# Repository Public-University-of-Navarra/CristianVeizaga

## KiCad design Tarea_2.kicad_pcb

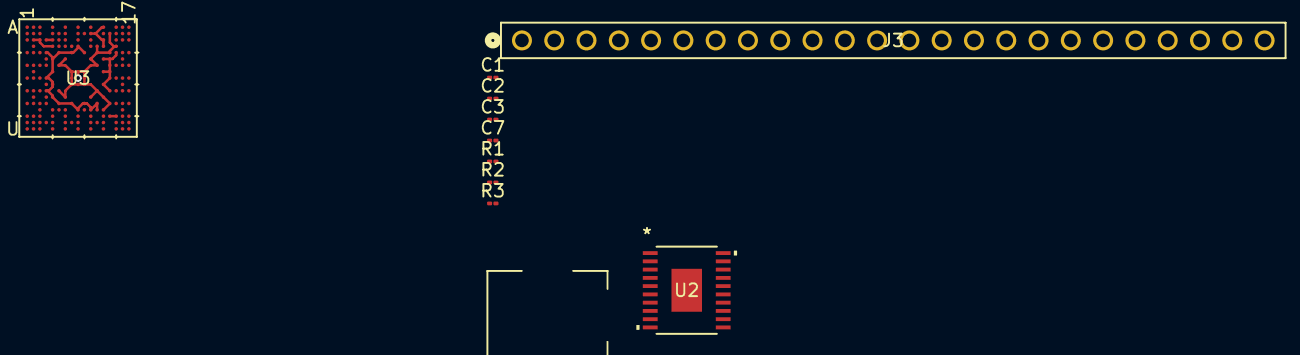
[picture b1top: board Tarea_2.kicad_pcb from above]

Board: 4 copper layers, 11 parts (0 on the bottom side), 9 nets.

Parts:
C1, C2, C3: 100n; C_01005_0402Metric
C7: 4.7u; C_01005_0402Metric
J1: 54-00166; CONN3_54-00166_TEN
J3: PPTC241LFBN-RC; CONN24_PPTC241LFBN-RC_SUL
R1, R2, R3: 1k; R_01005_0402Metric
U2: TPS75318QPWPRQ1; PWP20_3P38X2P4_TEX-L
U3: MIMXRT685SFVKB; VFBGA176_SOT1850-1_NXP-L

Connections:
/Alimentacion/V5: U2.3 (IN), U2.4 (IN)
/Alimentacion/V18: C7.1, U2.7 (FB/SENSE), U2.8 (OUTPUT), U2.9 (OUTPUT), U3.A13 (VDD1V8_1), U3.B11 (VDD1V8), U3.C4 (VDDA_BIAS), U3.C5 (VDDCORE), U3.C13 (VDD_AO1V8), U3.C16 (VDD1V8), U3.C17 (VDD1V8), U3.D2 (VREFP), U3.D9 (VDDCORE), U3.D13 (VDD_AO1V8), U3.E4 (VDDA_ADC1V8), U3.E6 (VDDIO_1), U3.E8 (VDDIO_1), U3.E10 (VDDIO_1), U3.E15 (VDD1V8), U3.F5 (VDDIO_0), U3.F13 (VDD1V8), U3.F14 (VDDCORE), U3.G14 (VDD1V8), U3.H5 (VDDIO_0), U3.H13 (VDDIO_1), U3.H14 (VDDIO_1), U3.J4 (VDDCORE), U3.J14 (VDDCORE), U3.K5 (VDDIO_0), U3.K13 (VDDIO_1), U3.L4 (VDD1V8), U3.L14 (VDDIO_1), U3.M5 (VDDIO_0), U3.N6 (VDDIO_0), U3.N8 (VDDIO_0), U3.N10 (VDDIO_0), U3.N12 (VDDIO_2), U3.P9 (VDDCORE), U3.P11 (VDDIO_2), U3.P12 (VDDIO_2), U3.R5 (VDDCORE), U3.R14 (VDDCORE), U3.R15 (VDD1V8)
GND: C1.2, C2.2, C3.2, C7.2, U2.5 (*EN), U2.17 (GND), U3.A16 (LDO_ENABLE), U3.B14 (XTALIN), U3.B17 (RTCXIN), U3.C2 (VREFN), U3.C3 (VSSA), U3.D5 (VSS), U3.D12 (VSSA), U3.D15 (VSS), U3.E12 (VSS), U3.E14 (VSS), U3.F7 (VSS), U3.F11 (VSS), U3.G6 (VSS), U3.G12 (VSS), U3.H8 (VSS), U3.H9 (VSS), U3.H10 (VSS), U3.J8 (VSS), U3.J10 (VSS), U3.K8 (VSS), U3.K9 (VSS), U3.K10 (VSS), U3.L6 (VSS), U3.L12 (VSS), U3.M7 (VSS), U3.M11 (VSS), U3.M13 (VSS), U3.N14 (VSS), U3.P13 (VSS)
unnamed: J3.22, R2.1
unnamed: J3.23, R3.1
unnamed: J3.24, R1.1
unnamed: C1.1, R1.2, U3.L16 (PIO2_24)
unnamed: C2.1, R3.2, U3.L17 (PIO2_25)
unnamed: C3.1, R2.2, U3.L15 (PIO2_26)
